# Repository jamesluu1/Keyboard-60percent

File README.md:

# Keyboard-60percent
A 60% keyboard with a 0.91inch oled display powered by a raspberry pi pico

Case 
Its a very simple clean aesthetic case which is going to be glued down 
Dimensions are 299 X 135 X 18

PCB

Schematic

Instructions

1.Add 61 cherry mx switches as well as all other components, wire them together and for switches make them into rows and column each row or column to a different gpio pin

2. Wire 0.91 inch oled display
  
3. turn into pcb and set up the layout including the stabilisers in their correct position
 
4.wire it up

5. Design a case

6.Create firmware

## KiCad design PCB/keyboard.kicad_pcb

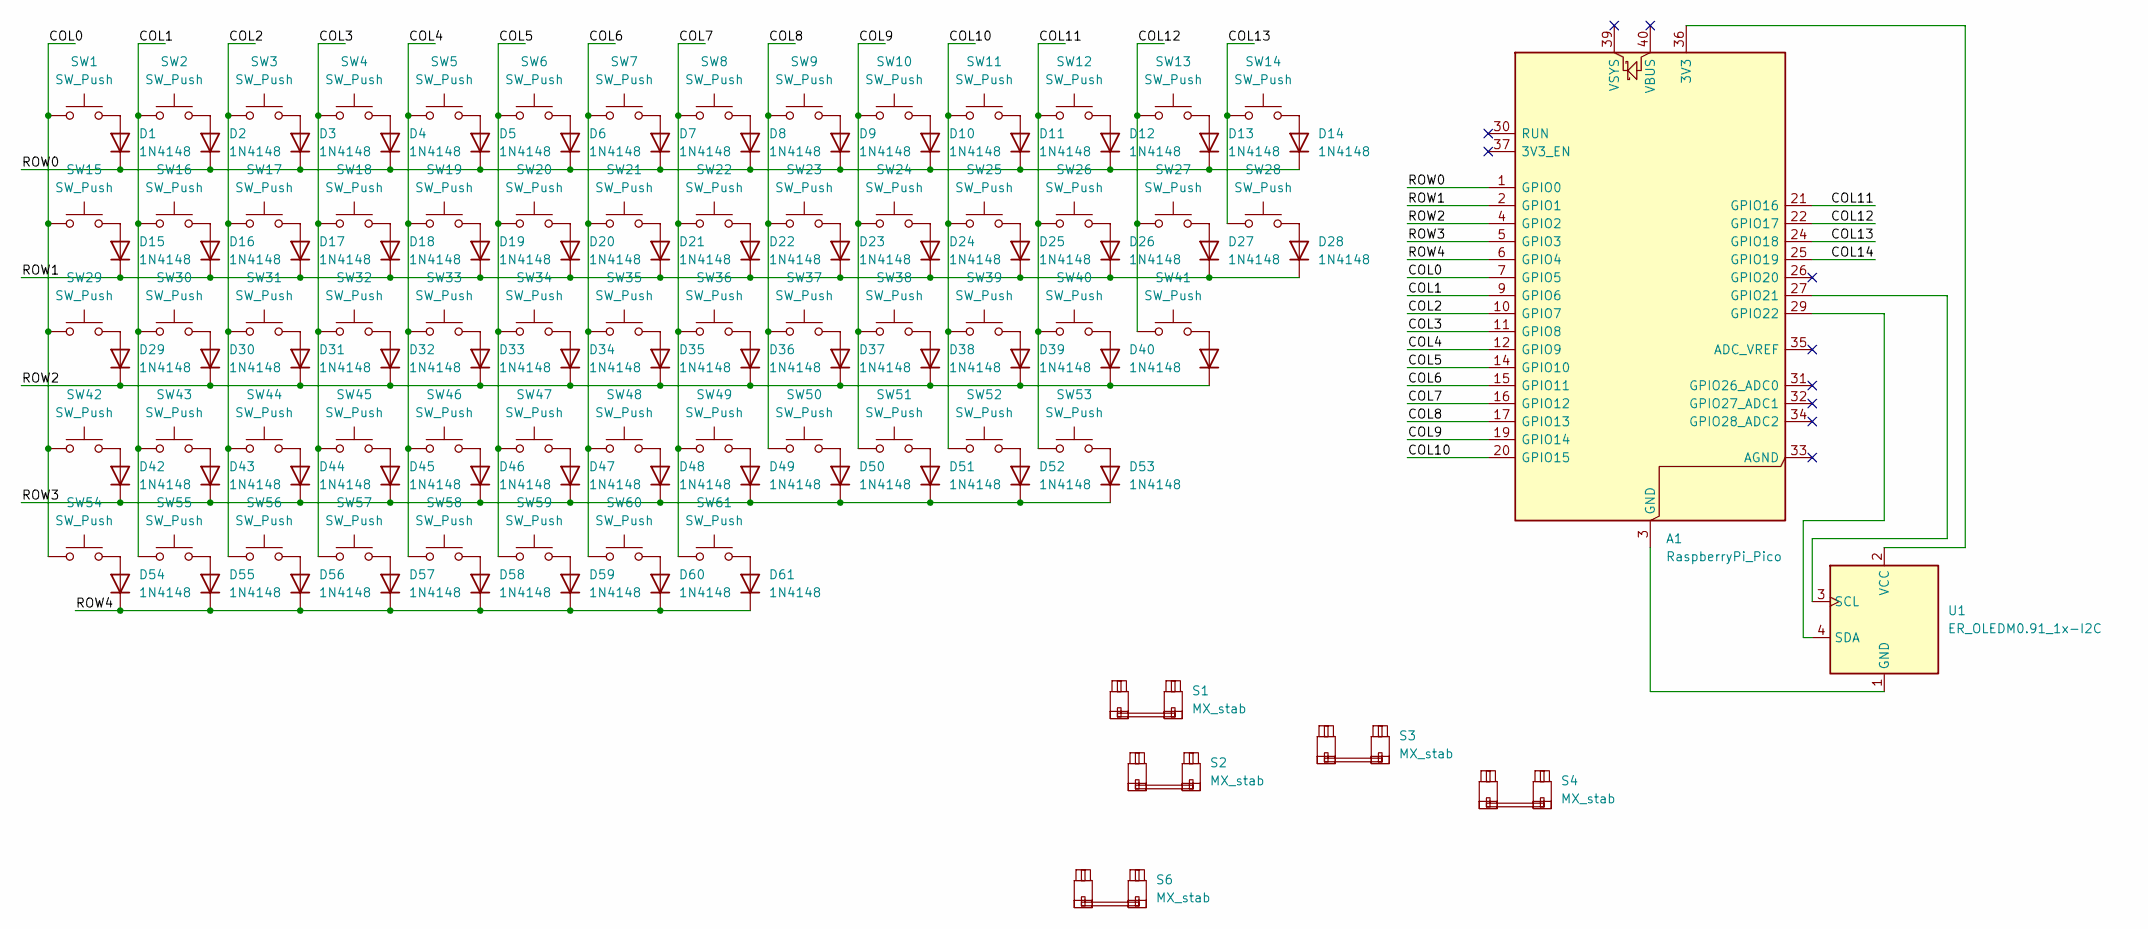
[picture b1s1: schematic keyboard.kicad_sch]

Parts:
A1: RaspberryPi_Pico; RaspberryPi_Pico_Common_THT
D1, D2, D3, D4, D5, D6, D7, D8, D9, D10, D11, D12, D13, D14, D15, D16, D17, D18, D19, D20, D21, D22, D23, D24, D25, D26, D27, D28, D29, D30, D31, D32, D33, D34, D35, D36, D37, D38, D39, D40, D41, D42, D43, D44, D45, D46, D47, D48, D49, D50, D51, D52, D53, D54, D55, D56, D57, D58, D59, D60, D61: 1N4148; D_DO-35_SOD27_P7.62mm_Horizontal
S1: MX_stab; STAB_MX_2u
S2, S3: MX_stab; STAB_MX_2.25u
S4: MX_stab; STAB_MX_2.75u
S6: MX_stab; STAB_MX_P_6.25u
SW1, SW2, SW3, SW4, SW5, SW6, SW7, SW8, SW9, SW10, SW11, SW12, SW13, SW14, SW15, SW16, SW17, SW18, SW19, SW20, SW21, SW22, SW23, SW24, SW25, SW26, SW27, SW28, SW29, SW30, SW31, SW32, SW33, SW34, SW35, SW36, SW37, SW38, SW39, SW40, SW41, SW42, SW43, SW44, SW45, SW46, SW47, SW48, SW49, SW50, SW51, SW52, SW53, SW54, SW55, SW56, SW57, SW58, SW59, SW60, SW61: SW_Push; SW_MX_1u
U1: ER_OLEDM0.91_1x-I2C

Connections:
/COL0: A1.7 (GPIO5), SW1.1, SW15.1, SW29.1, SW42.1, SW54.1
/COL1: A1.9 (GPIO6), SW2.1, SW16.1, SW30.1, SW43.1, SW55.1
/COL2: A1.10 (GPIO7), SW3.1, SW17.1, SW31.1, SW44.1, SW56.1
/COL3: A1.11 (GPIO8), SW4.1, SW18.1, SW32.1, SW45.1, SW57.1
/COL4: A1.12 (GPIO9), SW5.1, SW19.1, SW33.1, SW46.1, SW58.1
/COL5: A1.14 (GPIO10), SW6.1, SW20.1, SW34.1, SW47.1, SW59.1
/COL6: A1.15 (GPIO11), SW7.1, SW21.1, SW35.1, SW48.1, SW60.1
/COL7: A1.16 (GPIO12), SW8.1, SW22.1, SW36.1, SW49.1, SW61.1
/COL8: A1.17 (GPIO13), SW9.1, SW23.1, SW37.1, SW50.1
/COL9: A1.19 (GPIO14), SW10.1, SW24.1, SW38.1, SW51.1
/COL10: A1.20 (GPIO15), SW11.1, SW25.1, SW39.1, SW52.1
/COL11: A1.21 (GPIO16), SW12.1, SW26.1, SW40.1, SW53.1
/COL12: A1.22 (GPIO17), SW13.1, SW27.1, SW41.1
/COL13: A1.24 (GPIO18), SW14.1, SW28.1
/COL14: A1.25 (GPIO19)
/ROW0: A1.1 (GPIO0), D1.1 (K), D2.1 (K), D3.1 (K), D4.1 (K), D5.1 (K), D6.1 (K), D7.1 (K), D8.1 (K), D9.1 (K), D10.1 (K), D11.1 (K), D12.1 (K), D13.1 (K), D14.1 (K)
/ROW1: A1.2 (GPIO1), D15.1 (K), D16.1 (K), D17.1 (K), D18.1 (K), D19.1 (K), D20.1 (K), D21.1 (K), D22.1 (K), D23.1 (K), D24.1 (K), D25.1 (K), D26.1 (K), D27.1 (K), D28.1 (K)
/ROW2: A1.4 (GPIO2), D29.1 (K), D30.1 (K), D31.1 (K), D32.1 (K), D33.1 (K), D34.1 (K), D35.1 (K), D36.1 (K), D37.1 (K), D38.1 (K), D39.1 (K), D40.1 (K), D41.1 (K)
/ROW3: A1.5 (GPIO3), D42.1 (K), D43.1 (K), D44.1 (K), D45.1 (K), D46.1 (K), D47.1 (K), D48.1 (K), D49.1 (K), D50.1 (K), D51.1 (K), D52.1 (K), D53.1 (K)
/ROW4: A1.6 (GPIO4), D54.1 (K), D55.1 (K), D56.1 (K), D57.1 (K), D58.1 (K), D59.1 (K), D60.1 (K), D61.1 (K)
unnamed: A1.36 (3V3), U1.2 (VCC)
unnamed: A1.27 (GPIO21), U1.3 (SCL)
unnamed: A1.29 (GPIO22), U1.4 (SDA)
unnamed: D1.2 (A), SW1.2
unnamed: D2.2 (A), SW2.2
unnamed: D3.2 (A), SW3.2
unnamed: D4.2 (A), SW4.2
unnamed: D5.2 (A), SW5.2
unnamed: D6.2 (A), SW6.2
unnamed: D7.2 (A), SW7.2
unnamed: D8.2 (A), SW8.2
unnamed: D9.2 (A), SW9.2
unnamed: D10.2 (A), SW10.2
unnamed: D11.2 (A), SW11.2
unnamed: D12.2 (A), SW12.2
unnamed: D13.2 (A), SW13.2
unnamed: D14.2 (A), SW14.2
unnamed: D15.2 (A), SW15.2
unnamed: D16.2 (A), SW16.2
unnamed: D17.2 (A), SW17.2
unnamed: D18.2 (A), SW18.2
unnamed: D19.2 (A), SW19.2
unnamed: D20.2 (A), SW20.2
unnamed: D21.2 (A), SW21.2
unnamed: D22.2 (A), SW22.2
unnamed: D23.2 (A), SW23.2
unnamed: D24.2 (A), SW24.2
unnamed: D25.2 (A), SW25.2
unnamed: D26.2 (A), SW26.2
unnamed: D27.2 (A), SW27.2
unnamed: D28.2 (A), SW28.2
unnamed: D29.2 (A), SW29.2
unnamed: D30.2 (A), SW30.2
unnamed: D31.2 (A), SW31.2
unnamed: D32.2 (A), SW32.2
unnamed: D33.2 (A), SW33.2
unnamed: D34.2 (A), SW34.2
unnamed: D35.2 (A), SW35.2
unnamed: D36.2 (A), SW36.2
unnamed: D37.2 (A), SW37.2
unnamed: D38.2 (A), SW38.2
unnamed: D39.2 (A), SW39.2
unnamed: D40.2 (A), SW40.2
unnamed: D41.2 (A), SW41.2
unnamed: D42.2 (A), SW42.2
unnamed: D43.2 (A), SW43.2
unnamed: D44.2 (A), SW44.2
unnamed: D45.2 (A), SW45.2
unnamed: D46.2 (A), SW46.2
unnamed: D47.2 (A), SW47.2
unnamed: D48.2 (A), SW48.2
unnamed: D49.2 (A), SW49.2
unnamed: D50.2 (A), SW50.2
unnamed: D51.2 (A), SW51.2
unnamed: D52.2 (A), SW52.2
unnamed: D53.2 (A), SW53.2
unnamed: D54.2 (A), SW54.2
unnamed: D55.2 (A), SW55.2
unnamed: D56.2 (A), SW56.2
unnamed: D57.2 (A), SW57.2
unnamed: D58.2 (A), SW58.2
unnamed: D59.2 (A), SW59.2
unnamed: D60.2 (A), SW60.2
unnamed: D61.2 (A), SW61.2
unnamed: A1.3 (GND), A1.8 (GND), A1.13 (GND), A1.18 (GND), A1.23 (GND), A1.28 (GND), A1.38 (GND), U1.1 (GND)

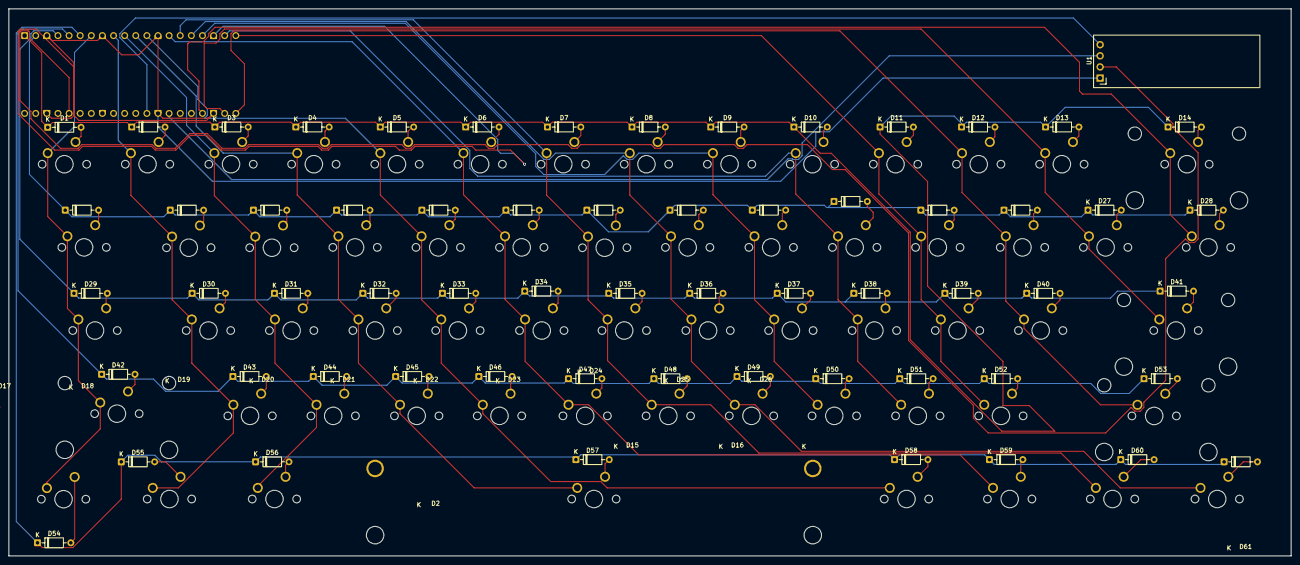
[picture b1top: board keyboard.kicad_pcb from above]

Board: 2 copper layers, 293.0 x 125.0 mm, 129 parts (1 on the bottom side), 84 nets.

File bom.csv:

Footprint,Quantity,Value
RaspberryPi_Pico_Common_THT,1,RaspberryPi_Pico
1N4148 Diode,61,1N4148
Stabiliser CHerry_MX_2u,1,MX_stab
Stabiliser CHerry_MX_2.25u,2,MX_stab
Stabiliser Cherry_MX_2.75u,1,MX_stab
Stabiliser Cherry_MX_P_6.25u,1,MX_stab
Switch Cherry_MX_1u,61,SW_Push
0.91 inch Oled display,1,ER_OLEDM0.91_1x-I2C
Custom 3d printed case,1, 3dprinted case
Custom PCB,1,Custom pcb design 60% keyboard
